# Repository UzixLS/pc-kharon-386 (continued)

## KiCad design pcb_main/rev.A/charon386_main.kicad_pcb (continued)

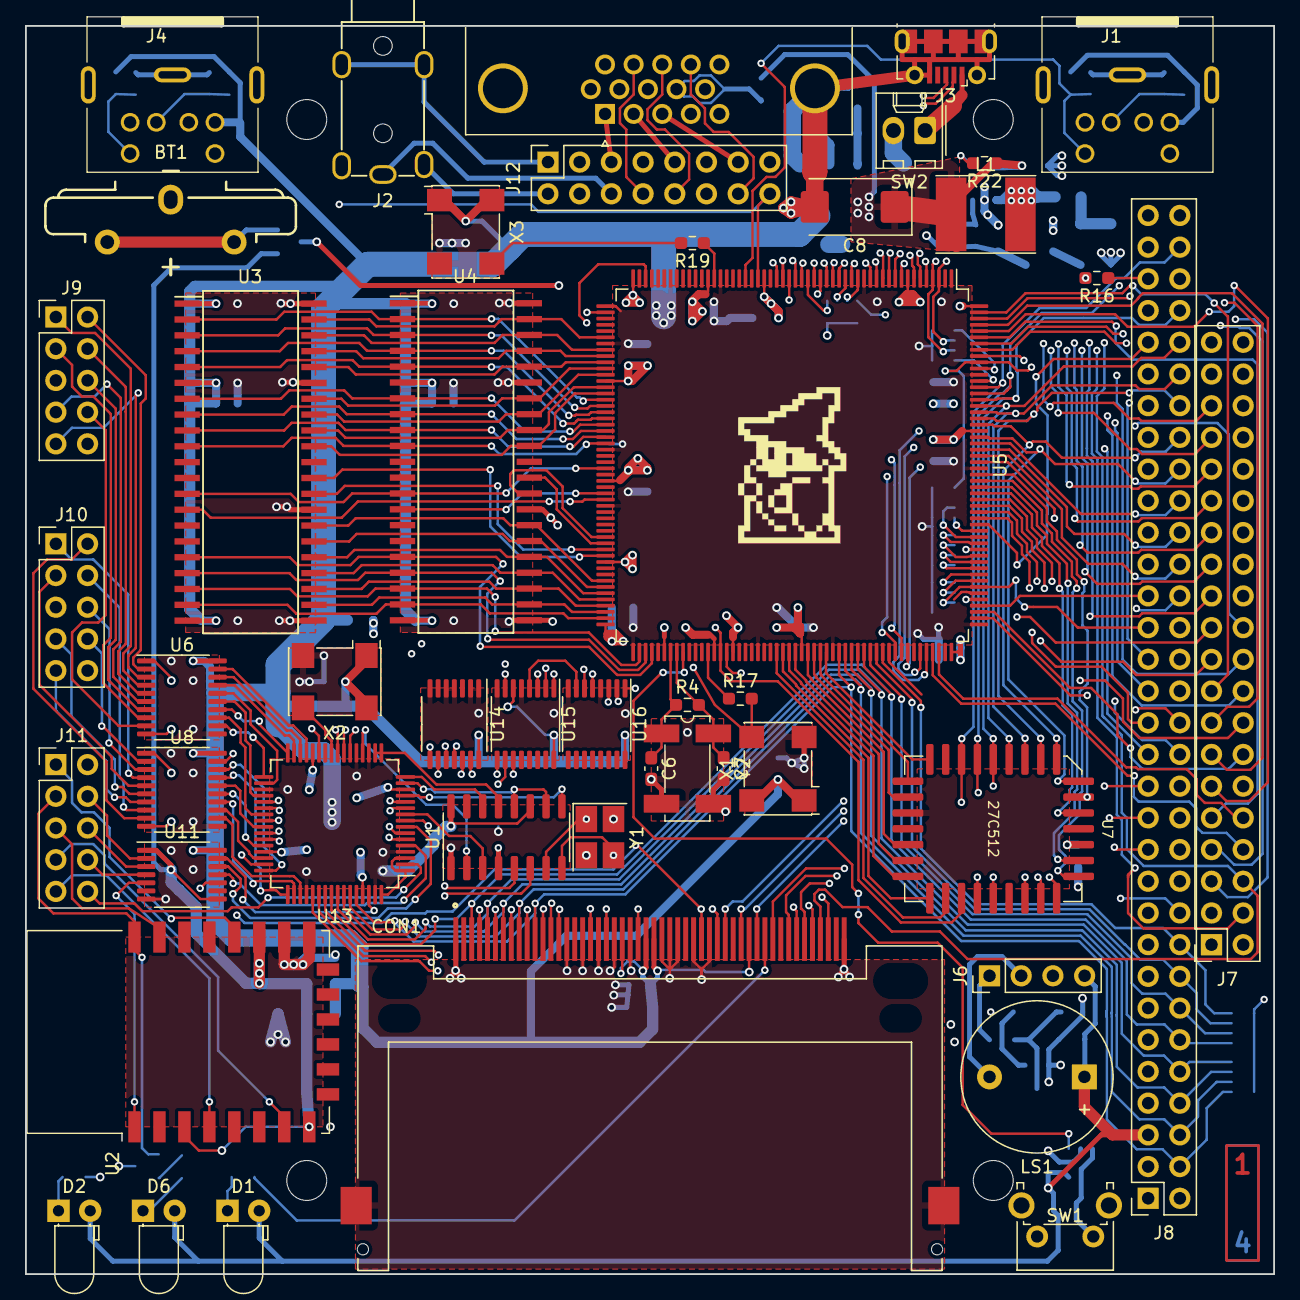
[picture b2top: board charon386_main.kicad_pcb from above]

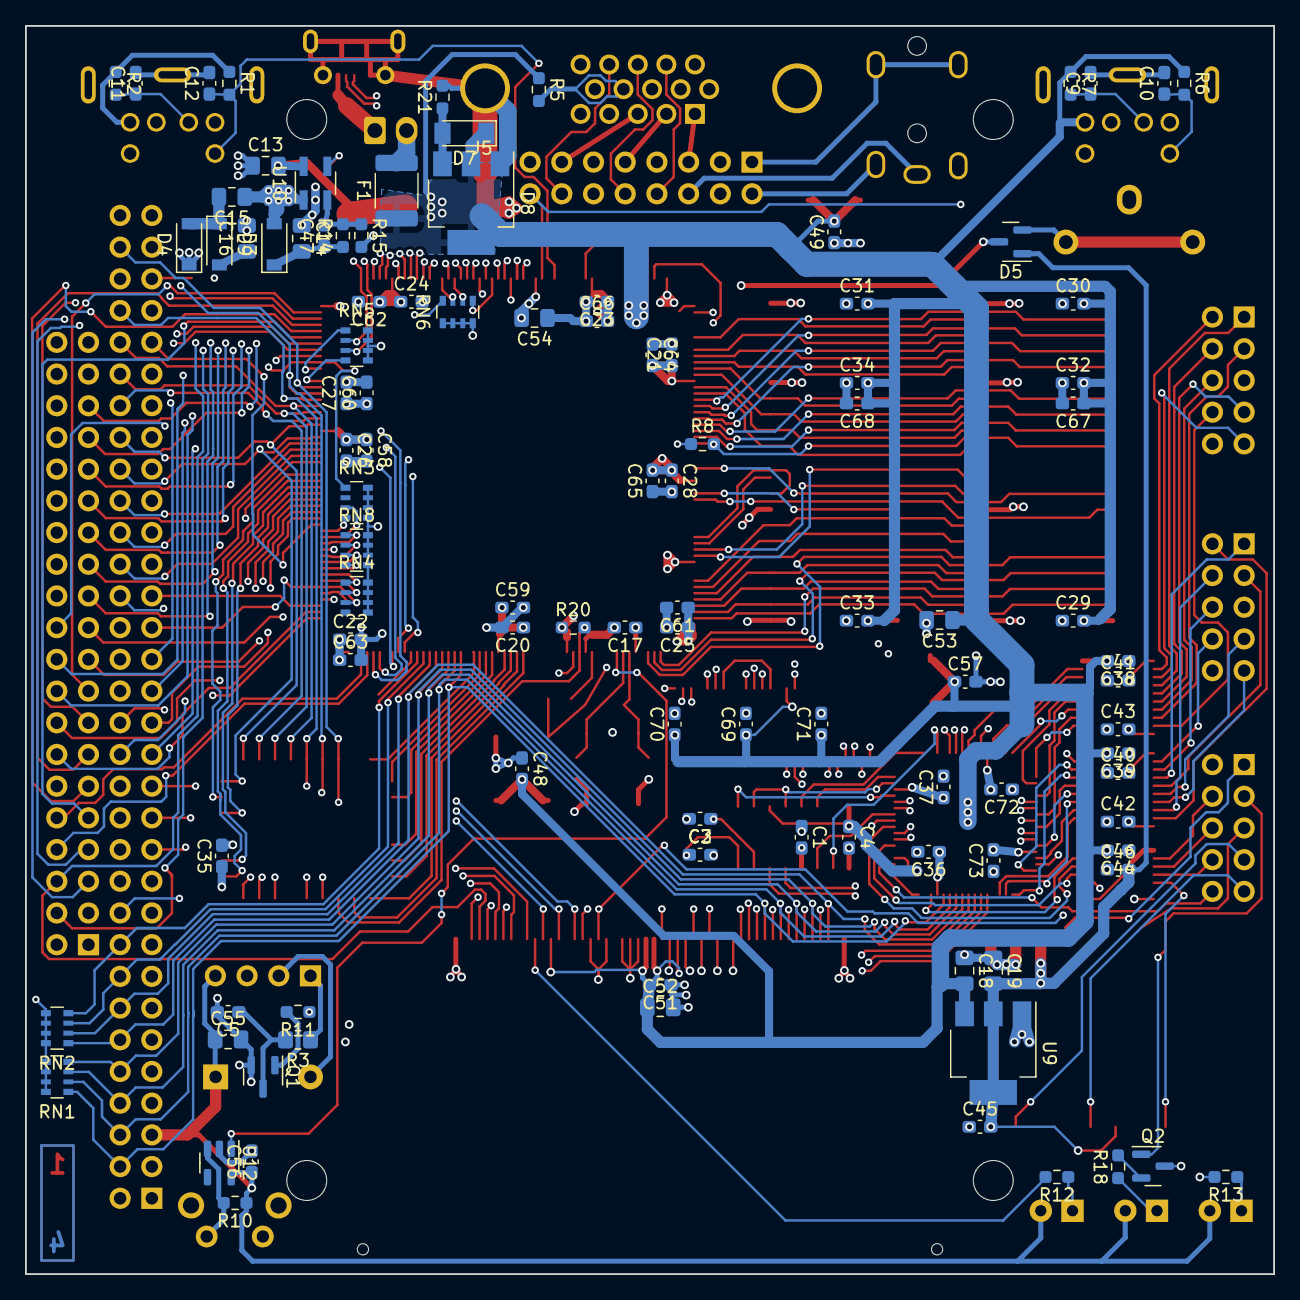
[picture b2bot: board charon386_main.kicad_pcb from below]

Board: 4 copper layers, 100.0 x 100.0 mm, 156 parts (104 on the bottom side), 245 nets.

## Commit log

2021-11-24 add .gitignore and .gitattributes
2021-11-24 pcb rev.A wip
2021-12-13 wip pcb rev.A
2022-06-17 wip pcb rev.A (almost done now)
2022-09-12 wip pcb rev.A; rename charon -> kharon
2022-09-22 pcb rev.A final version
2022-11-26 add errata
2023-02-19 add rom files
2023-09-16 add pcb_top rev.A1
2023-09-16 add pcb_main rev.A1
2023-09-16 add readme
2023-09-16 release all pcbs
2023-09-16 wip pcb rev.A1
2023-09-16 update all pcb rev.A1 files - minor changes
2023-09-16 add datasheets
2023-09-16 upload cf image
2023-09-16 add license
2024-09-27 shrink CF image to fit into some smaller cards
2024-11-06 update errata
2026-03-12 add readme for roms
2026-06-17 remove raw=true from README links
